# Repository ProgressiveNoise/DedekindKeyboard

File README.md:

# Dedekind, inspired by Cantor

- Infinite set of silly mathematical jokes.

- Permissive Open Hardware Licence - do whatever you want with it.

- Not just PCBs, this repo contains STEP for a decent and easy to print case.
  Your build will be very solid.

- Reversible, no need to order 10 boards.

- MX Hotswap.

- Robust through-hole USB-C socket for interconnection:

    - Very reliable.

    - Does not fry MCU I/Os by design.

    - Cables are available in every shop on the planet.

- Optional extra protection circuit.

- RP2040 is a powerful and well-supported MCU.

- Easy to source parts.

This keyboard is compact, reliable, and relatively easy to build. It is
diodeless, the protection circuit is optional. Only the TH USB-C connector
could be an annoyance for an inexperienced builder, but that’s it. Everything
else should be smooth.

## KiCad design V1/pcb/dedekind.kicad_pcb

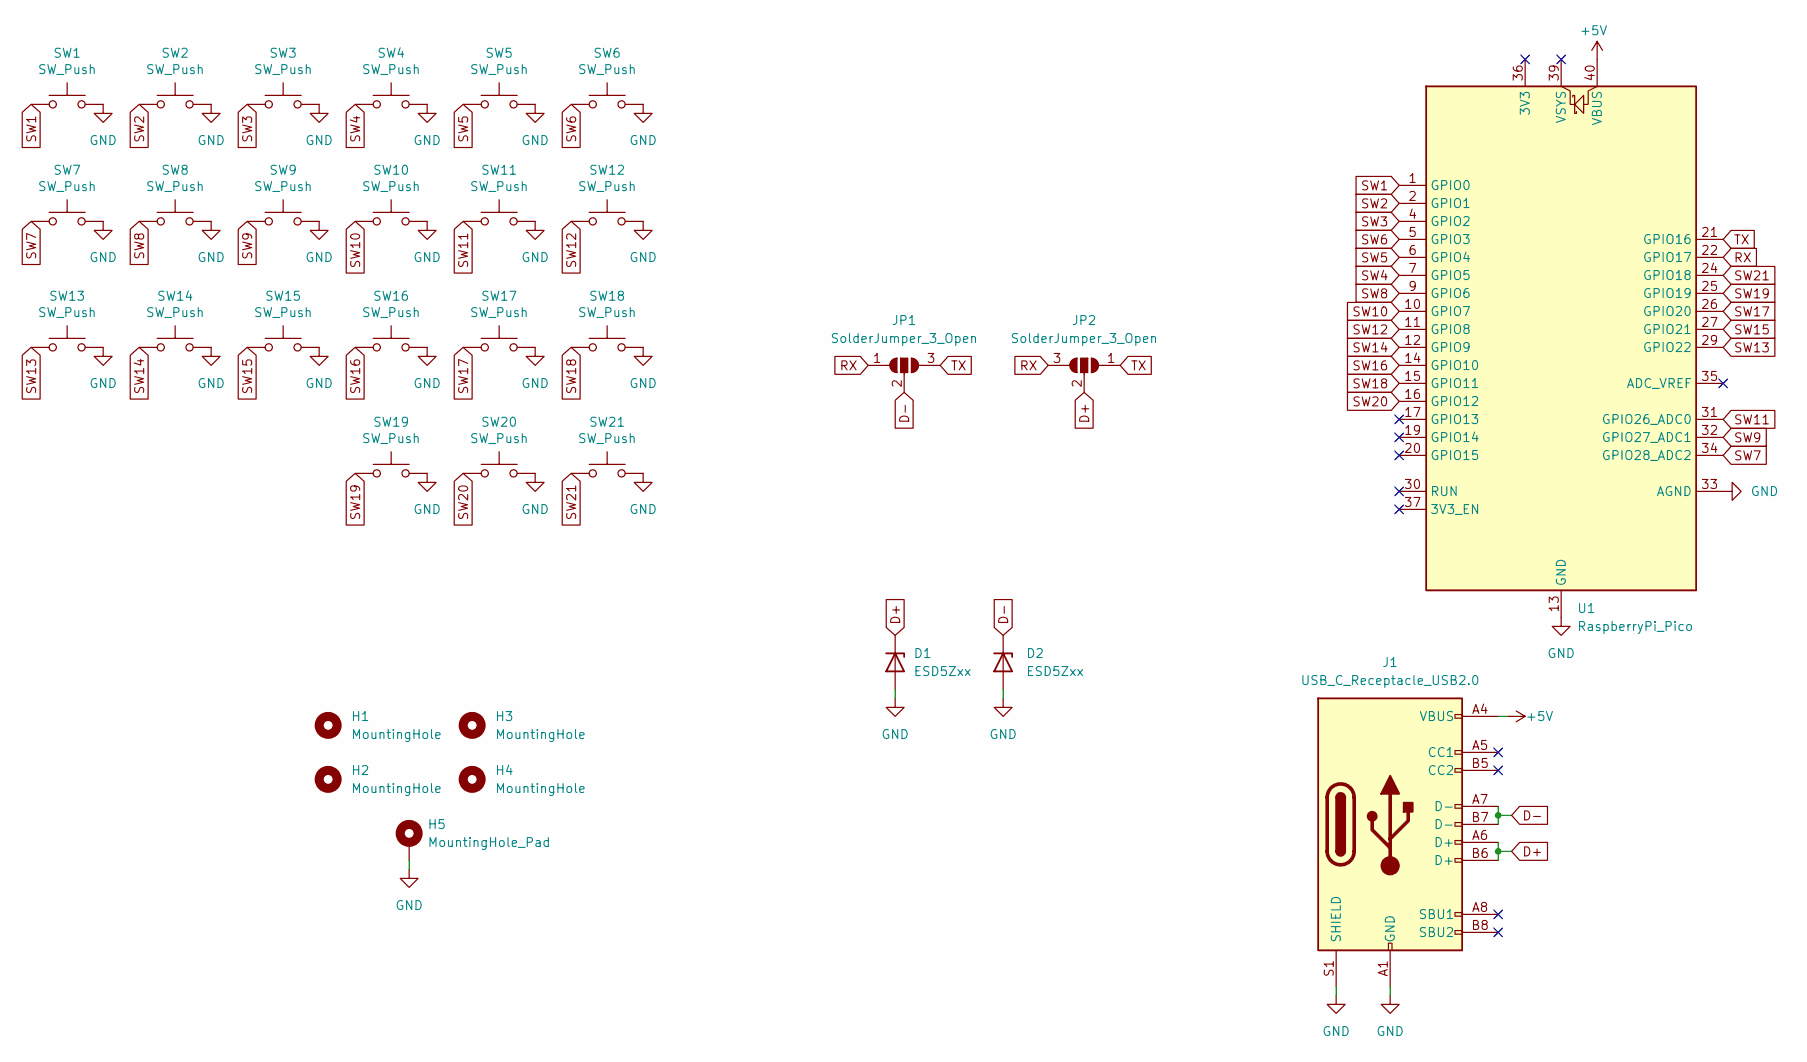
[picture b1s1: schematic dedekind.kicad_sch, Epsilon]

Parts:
D1, D2: ESD5Zxx; D_SOD-323_TH_HandSoldering
H1, H2, H3, H4: MountingHole; MountingHole_3.2mm_M3
H5: MountingHole_Pad; MountingHole_3.2mm_M3_DIN965_Pad
J1: USB_C_Receptacle_USB2.0; USB_C_Receptacle_JBL
JP1, JP2: SolderJumper_3_Open; R_0805_2012Metric_Pad1.20x1.40mm_Jumper_HandSolder
SW1, SW2, SW3, SW4, SW5, SW6, SW7, SW8, SW9, SW10, SW11, SW12, SW13, SW14, SW15, SW16, SW17, SW18, SW19, SW20, SW21: SW_Push; SW_Hotswap_Kailh_MX_DS_1.00u
U1: RaspberryPi_Pico; RaspberryPi_Pico_Common_Reversable

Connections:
+5V: J1.A4 (VBUS), J1.A9 (VBUS), J1.B4 (VBUS), J1.B9 (VBUS), U1.40 (VBUS)
D+: D1.1 (K), J1.A6 (D+), J1.B6 (D+), JP2.2 (C)
D-: D2.1 (K), J1.A7 (D-), J1.B7 (D-), JP1.2 (C)
GND: D1.2 (A), D2.2 (A), H5.1, J1.A1 (GND), J1.A12 (GND), J1.B1 (GND), J1.B12 (GND), J1.S1 (SHIELD), SW1.2, SW2.2, SW3.2, SW4.2, SW5.2, SW6.2, SW7.2, SW8.2, SW9.2, SW10.2, SW11.2, SW12.2, SW13.2, SW14.2, SW15.2, SW16.2, SW17.2, SW18.2, SW19.2, SW20.2, SW21.2, U1.3 (GND), U1.8 (GND), U1.13 (GND), U1.18 (GND), U1.23 (GND), U1.28 (GND), U1.33 (AGND), U1.38 (GND)
RX: JP1.1 (A), JP2.3 (B), U1.22 (GPIO17)
SW1: SW1.1, U1.1 (GPIO0)
SW2: SW2.1, U1.2 (GPIO1)
SW3: SW3.1, U1.4 (GPIO2)
SW4: SW4.1, U1.7 (GPIO5)
SW5: SW5.1, U1.6 (GPIO4)
SW6: SW6.1, U1.5 (GPIO3)
SW7: SW7.1, U1.34 (GPIO28_ADC2)
SW8: SW8.1, U1.9 (GPIO6)
SW9: SW9.1, U1.32 (GPIO27_ADC1)
SW10: SW10.1, U1.10 (GPIO7)
SW11: SW11.1, U1.31 (GPIO26_ADC0)
SW12: SW12.1, U1.11 (GPIO8)
SW13: SW13.1, U1.29 (GPIO22)
SW14: SW14.1, U1.12 (GPIO9)
SW15: SW15.1, U1.27 (GPIO21)
SW16: SW16.1, U1.14 (GPIO10)
SW17: SW17.1, U1.26 (GPIO20)
SW18: SW18.1, U1.15 (GPIO11)
SW19: SW19.1, U1.25 (GPIO19)
SW20: SW20.1, U1.16 (GPIO12)
SW21: SW21.1, U1.24 (GPIO18)
TX: JP1.3 (B), JP2.1 (A), U1.21 (GPIO16)

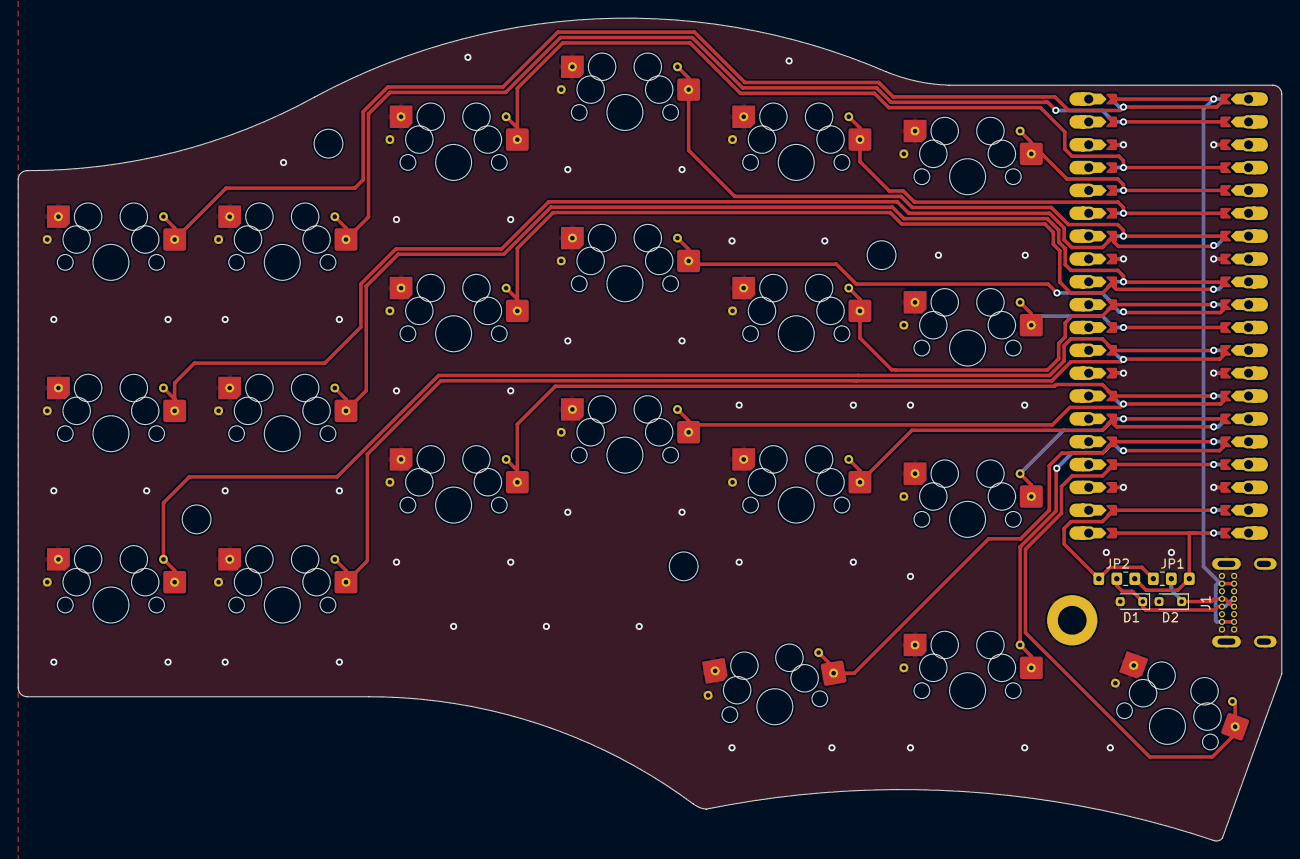
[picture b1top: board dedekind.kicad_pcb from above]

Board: 2 copper layers, 140.5 x 91.5 mm, 32 parts (0 on the bottom side), 27 nets.

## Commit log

2024-05-18 Public Init
2024-05-18 Init guide
2024-05-18 Test Images
2024-05-18 Doc photos
2024-05-18 Create LICENSE
2024-05-21 Python formatting
2024-05-21 Build guide update
2024-05-21 Main Photo
2024-05-21 Doc fixes
2024-05-21 Typos
